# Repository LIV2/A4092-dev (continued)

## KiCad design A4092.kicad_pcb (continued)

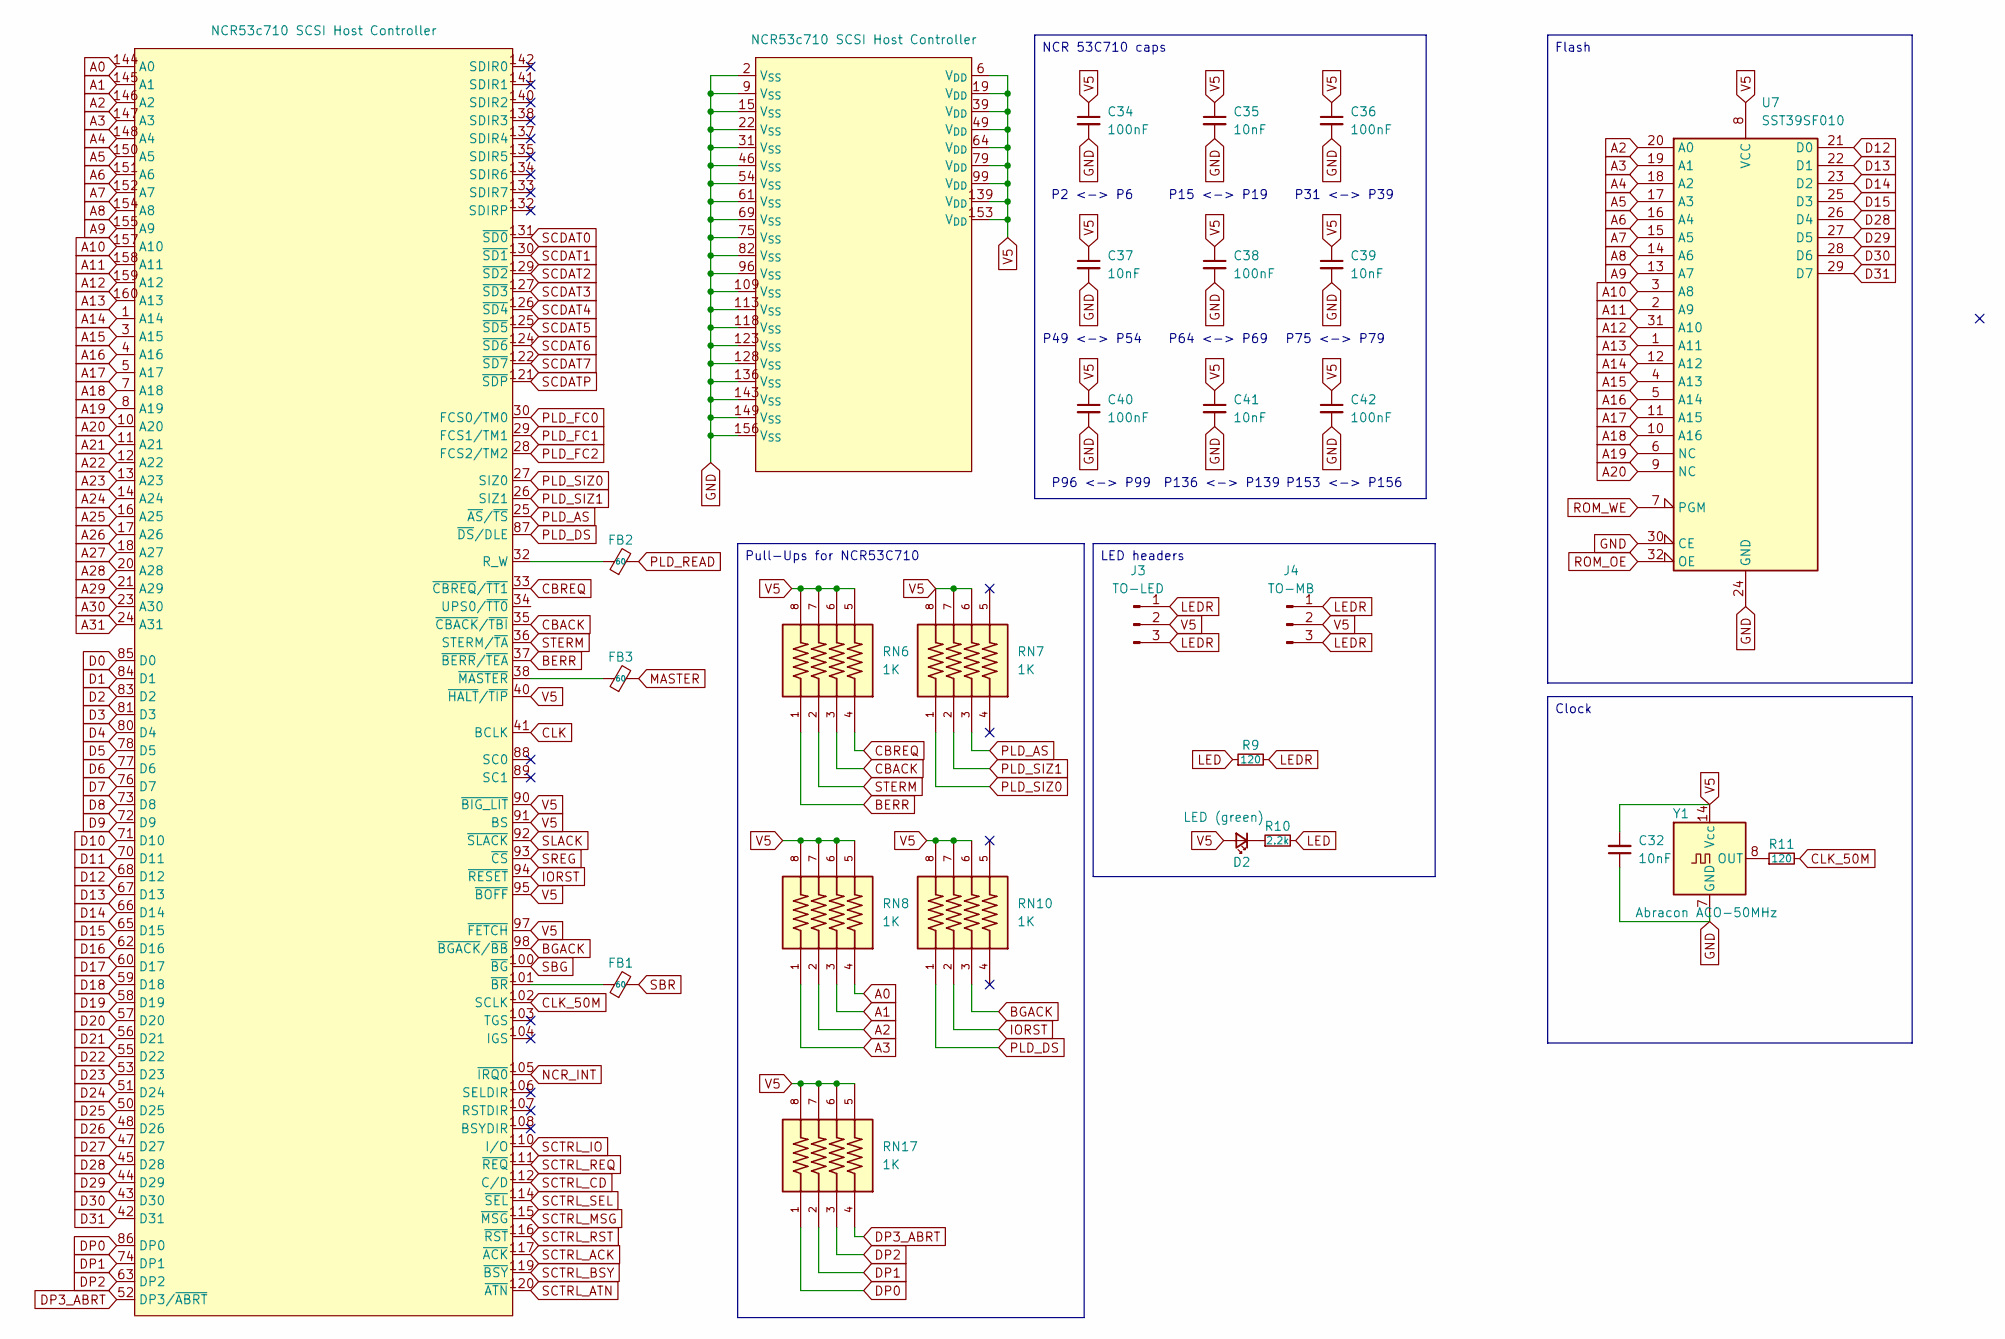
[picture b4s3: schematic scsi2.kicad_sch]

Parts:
C32, C35, C37, C39, C41: 10nF; C_0603_1608Metric_Pad1.08x0.95mm_HandSolder
C34, C36, C38, C40, C42: 100nF; C_0603_1608Metric_Pad1.08x0.95mm_HandSolder
D2: LED (green); LED_0805_2012Metric
FB1, FB2, FB3: 60; C_0603_1608Metric_Pad1.08x0.95mm_HandSolder
J3: TO-LED; PinHeader_1x03_P2.54mm_Vertical
J4: TO-MB; PinHeader_1x03_P2.54mm_Vertical
R9, R11: 120; R_0603_1608Metric
R10: 2.2k; R_0603_1608Metric
RN6, RN7, RN8, RN10, RN17: 1K; BO_CAY16; PARTREV V.9
U4: NCR53c710 SCSI Host Controller; PQFP-160_28x28mm_P0.65mm
U7: SST39SF010; TSSOP-32_8x11mm_P0.65mm
Y1: Abracon ACO-50MHz; Oscillator_DIP-14

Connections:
A0: RN8.4, U4.144 (A0); also elsewhere on the board
A1: RN8.3, U4.145 (A1); also elsewhere on the board
A2: RN8.2, U4.146 (A2), U7.20 (A0); also elsewhere on the board
A3: RN8.1, U4.147 (A3), U7.19 (A1); also elsewhere on the board
A4: U4.148 (A4), U7.18 (A2); also elsewhere on the board
A5: U4.150 (A5), U7.17 (A3); also elsewhere on the board
A6: U4.151 (A6), U7.16 (A4); also elsewhere on the board
A7: U4.152 (A7), U7.15 (A5); also elsewhere on the board
A8: U4.154 (A8), U7.14 (A6); also elsewhere on the board
A9: U4.155 (A9), U7.13 (A7); also elsewhere on the board
A10: U4.157 (A10), U7.3 (A8); also elsewhere on the board
A11: U4.158 (A11), U7.2 (A9); also elsewhere on the board
A12: U4.159 (A12), U7.31 (A10); also elsewhere on the board
A13: U4.160 (A13), U7.1 (A11); also elsewhere on the board
A14: U4.1 (A14), U7.12 (A12); also elsewhere on the board
A15: U4.3 (A15), U7.4 (A13); also elsewhere on the board
A16: U4.4 (A16), U7.5 (A14); also elsewhere on the board
A17: U4.5 (A17), U7.11 (A15); also elsewhere on the board
A18: U4.7 (A18), U7.10 (A16); also elsewhere on the board
A19: U4.8 (A19), U7.6 (NC); also elsewhere on the board
A20: U4.10 (A20), U7.9 (NC); also elsewhere on the board
A21: U4.11 (A21); also elsewhere on the board
A22: U4.12 (A22); also elsewhere on the board
A23: U4.13 (A23); also elsewhere on the board
A24: U4.14 (A24); also elsewhere on the board
A25: U4.16 (A25); also elsewhere on the board
A26: U4.17 (A26); also elsewhere on the board
A27: U4.18 (A27); also elsewhere on the board
A28: U4.20 (A28); also elsewhere on the board
A29: U4.21 (A29); also elsewhere on the board
A30: U4.23 (A30); also elsewhere on the board
A31: U4.24 (A31); also elsewhere on the board
BERR: RN6.1, U4.37 (~BERR/~TEA); also elsewhere on the board
BGACK: RN10.3, U4.98 (~BGACK/~BB)
CBACK: RN6.3, U4.35 (~CBACK/~TBI); also elsewhere on the board
CBREQ: RN6.4, U4.33 (~CBREQ/~TT1); also elsewhere on the board
CLK: U4.41 (BCLK); also elsewhere on the board
CLK_50M: R11.2, U4.102 (SCLK); also elsewhere on the board
D0: U4.85 (D0); also elsewhere on the board
D1: U4.84 (D1); also elsewhere on the board
D2: U4.83 (D2); also elsewhere on the board
D3: U4.81 (D3); also elsewhere on the board
D4: U4.80 (D4); also elsewhere on the board
D5: U4.78 (D5); also elsewhere on the board
D6: U4.77 (D6); also elsewhere on the board
D7: U4.76 (D7); also elsewhere on the board
D8: U4.73 (D8); also elsewhere on the board
D9: U4.72 (D9); also elsewhere on the board
D10: U4.71 (D10); also elsewhere on the board
D11: U4.70 (D11); also elsewhere on the board
D12: U4.68 (D12), U7.21 (D0); also elsewhere on the board
D13: U4.67 (D13), U7.22 (D1); also elsewhere on the board
D14: U4.66 (D14), U7.23 (D2); also elsewhere on the board
D15: U4.65 (D15), U7.25 (D3); also elsewhere on the board
D16: U4.62 (D16); also elsewhere on the board
D17: U4.60 (D17); also elsewhere on the board
D18: U4.59 (D18); also elsewhere on the board
D19: U4.58 (D19); also elsewhere on the board
D20: U4.57 (D20); also elsewhere on the board
D21: U4.56 (D21); also elsewhere on the board
D22: U4.55 (D22); also elsewhere on the board
D23: U4.53 (D23); also elsewhere on the board
D24: U4.51 (D24); also elsewhere on the board
D25: U4.50 (D25); also elsewhere on the board
D26: U4.48 (D26); also elsewhere on the board
D27: U4.47 (D27); also elsewhere on the board
D28: U4.45 (D28), U7.26 (D4); also elsewhere on the board
D29: U4.44 (D29), U7.27 (D5); also elsewhere on the board
D30: U4.43 (D30), U7.28 (D6); also elsewhere on the board
D31: U4.42 (D31), U7.29 (D7); also elsewhere on the board
DP0: RN17.1, U4.86 (DP0)
DP1: RN17.2, U4.74 (DP1)
DP2: RN17.3, U4.63 (DP2)
DP3_ABRT: RN17.4, U4.52 (DP3/~ABRT)
IORST: RN10.2, U4.94 (~RESET); also elsewhere on the board
LED: R9.1, R10.2; also elsewhere on the board
LEDR: J3.1, J3.3, J4.1, J4.3, R9.2; also elsewhere on the board
MASTER: FB3.2; also elsewhere on the board
NCR_INT: U4.105 (~IRQ0); also elsewhere on the board
unnamed: D2.1 (K), R10.1
unnamed: FB2.1, U4.32 (R_W)
unnamed: FB1.1, U4.101 (~BR)
unnamed: FB3.1, U4.38 (~MASTER)
unnamed: R11.1, Y1.3 (OUT), Y1.8 (OUT)
PLD_AS: RN7.3, U4.25 (~AS/~TS); also elsewhere on the board
PLD_DS: RN10.1, U4.87 (~DS/DLE); also elsewhere on the board
PLD_FC0: U4.30 (FCS0/TM0); also elsewhere on the board
PLD_FC1: U4.29 (FCS1/TM1); also elsewhere on the board
PLD_FC2: U4.28 (FCS2/TM2); also elsewhere on the board
PLD_READ: FB2.2; also elsewhere on the board
PLD_SIZ0: RN7.1, U4.27 (SIZ0); also elsewhere on the board
PLD_SIZ1: RN7.2, U4.26 (SIZ1); also elsewhere on the board
ROM_OE: U7.32 (OE); also elsewhere on the board
ROM_WE: U7.7 (PGM)
SBG: U4.100 (~BG); also elsewhere on the board
SBR: FB1.2; also elsewhere on the board
SCDAT0: U4.131 (~SD0); also elsewhere on the board
SCDAT1: U4.130 (~SD1); also elsewhere on the board
SCDAT2: U4.129 (~SD2); also elsewhere on the board
SCDAT3: U4.127 (~SD3); also elsewhere on the board
SCDAT4: U4.126 (~SD4); also elsewhere on the board
SCDAT5: U4.125 (~SD5); also elsewhere on the board
SCDAT6: U4.124 (~SD6); also elsewhere on the board
SCDAT7: U4.122 (~SD7); also elsewhere on the board
SCDATP: U4.121 (~SDP); also elsewhere on the board
SCTRL_ACK: U4.117 (~ACK); also elsewhere on the board
SCTRL_ATN: U4.120 (~ATN); also elsewhere on the board
SCTRL_BSY: U4.119 (~BSY); also elsewhere on the board
SCTRL_CD: U4.112 (C/D); also elsewhere on the board
SCTRL_IO: U4.110 (I/O); also elsewhere on the board
SCTRL_MSG: U4.115 (~MSG); also elsewhere on the board
SCTRL_REQ: U4.111 (~REQ); also elsewhere on the board
SCTRL_RST: U4.116 (~RST); also elsewhere on the board
SCTRL_SEL: U4.114 (~SEL); also elsewhere on the board
SLACK: U4.92 (~SLACK); also elsewhere on the board
SREG: U4.93 (~CS); also elsewhere on the board
STERM: RN6.2, U4.36 (STERM/~TA); also elsewhere on the board
V5: C32.2, C34.1, C35.1, C36.1, C37.1, C38.1, C39.1, C40.1, C41.1, C42.1, D2.2 (A), J3.2, J4.2, RN6.5, RN6.6, RN6.7, RN6.8, RN7.6, RN7.7, RN7.8, RN8.5, RN8.6, RN8.7, RN8.8, RN10.6, RN10.7, RN10.8, RN17.5, RN17.6, RN17.7, RN17.8, U4.6 (V_{DD}), U4.19 (V_{DD}), U4.39 (V_{DD}), U4.40 (~HALT/~TIP), U4.49 (V_{DD}), U4.64 (V_{DD}), U4.79 (V_{DD}), U4.90 (~BIG_LIT), U4.91 (BS), U4.95 (~BOFF), U4.97 (~FETCH), U4.99 (V_{DD}), U4.139 (V_{DD}), U4.153 (V_{DD}), U7.8 (VCC), Y1.4 (VDD), Y1.14 (Vcc); also elsewhere on the board

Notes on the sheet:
P2 <-> P6
P96 <-> P99
P49 <-> P54
P136 <-> P139
P153 <-> P156
P31 <-> P39
P64 <-> P69
P15 <-> P19
P75 <-> P79
LED headers
NCR 53C710 caps
Clock
Flash
Pull-Ups for NCR53C710

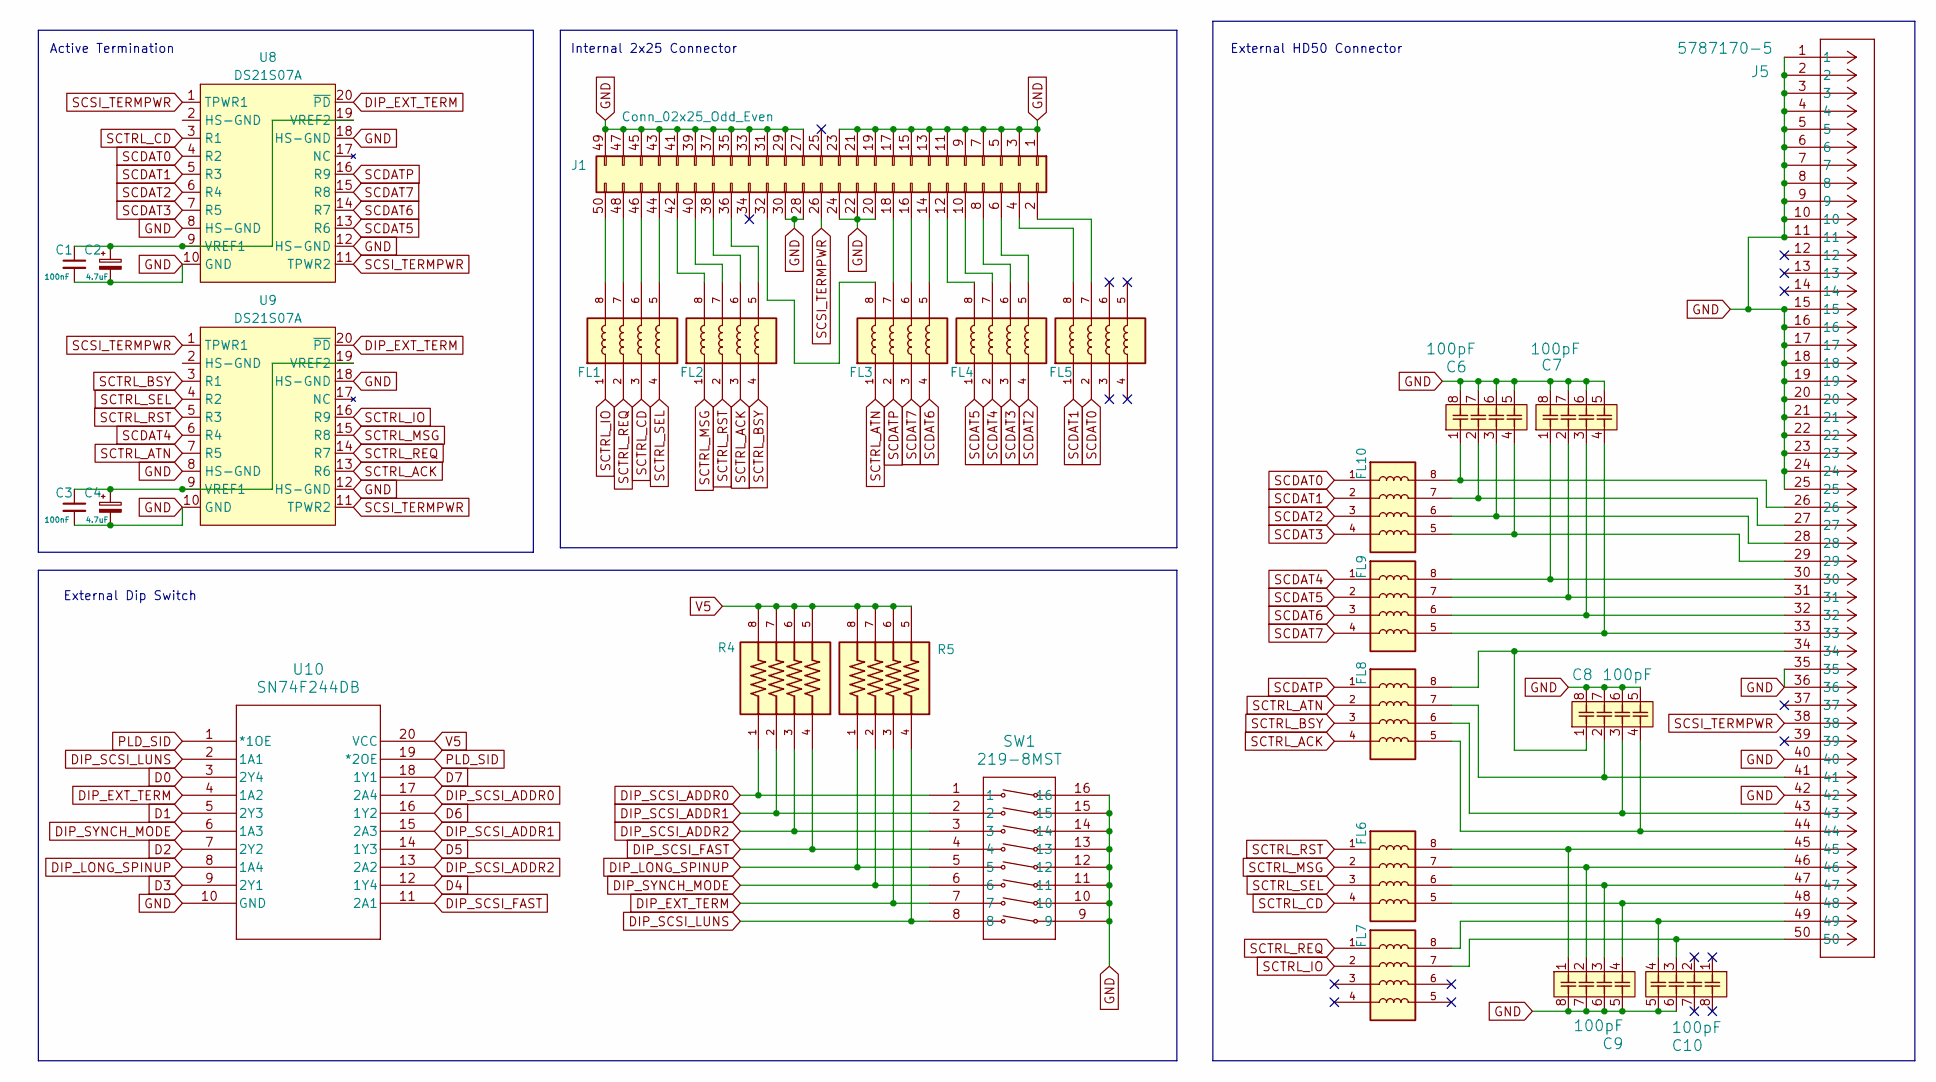
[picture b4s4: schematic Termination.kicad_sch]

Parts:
C1, C3: 100nF; C_0603_1608Metric_Pad1.08x0.95mm_HandSolder
C2, C4: 4.7uF; CP_Elec_4x5.7
C6, C7, C8, C9, C10: 100pF; CAP_CA0612_3P2X1P6_YAG
FL1, FL2, FL3, FL4, FL5, FL6, FL7, FL8, FL9, FL10: DA1206D600R-10; FB_DA1206D600R-10; PARTREV F; DigiKey_Part_Number 240-2539-2-ND
J1: Conn_02x25_Odd_Even; IDC-Header_2x25_P2.54mm_Vertical
J5: 5787170-5; CONN_5787170-5_TYC
R4, R5: YC324-FK-071KL; RESCAXS127P508X320X70-8N; PARTREV V.9
SW1: 219-8MST; SO16_219-8_CTS
U8, U9: DS21S07A; TSSOP-20_4.4x6.5mm_P0.65mm
U10: SN74F244DB; DB20

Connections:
D0: U10.3 (2Y4); also elsewhere on the board
D1: U10.5 (2Y3); also elsewhere on the board
D2: U10.7 (2Y2); also elsewhere on the board
D3: U10.9 (2Y1); also elsewhere on the board
D4: U10.12 (1Y4); also elsewhere on the board
D5: U10.14 (1Y3); also elsewhere on the board
D6: U10.16 (1Y2); also elsewhere on the board
D7: U10.18 (1Y1); also elsewhere on the board
DIP_EXT_TERM: R5.3, SW1.7, U8.20 (~PD), U9.20 (~PD), U10.4 (1A2); also elsewhere on the board
DIP_LONG_SPINUP: R5.1, SW1.5, U10.8 (1A4); also elsewhere on the board
DIP_SCSI_ADDR0: R4.1, SW1.1, U10.17 (2A4); also elsewhere on the board
DIP_SCSI_ADDR1: R4.2, SW1.2, U10.15 (2A3); also elsewhere on the board
DIP_SCSI_ADDR2: R4.3, SW1.3, U10.13 (2A2); also elsewhere on the board
DIP_SCSI_FAST: R4.4, SW1.4, U10.11 (2A1); also elsewhere on the board
DIP_SCSI_LUNS: R5.4, SW1.8, U10.2 (1A1); also elsewhere on the board
DIP_SYNCH_MODE: R5.2, SW1.6, U10.6 (1A3); also elsewhere on the board
unnamed: C6.1, FL10.8, J5.26
unnamed: C6.2, FL10.7, J5.27
unnamed: C6.3, FL10.6, J5.28
unnamed: C6.4, FL10.5, J5.29
unnamed: C7.1, FL9.8, J5.30
unnamed: C7.2, FL9.7, J5.31
unnamed: C7.3, FL9.6, J5.32
unnamed: C7.4, FL9.5, J5.33
unnamed: C8.1, FL8.8, J5.34
unnamed: C8.2, FL8.7, J5.41
unnamed: C8.3, FL8.6, J5.43
unnamed: C8.4, FL8.5, J5.44
unnamed: C9.1, FL6.8, J5.45
unnamed: C9.2, FL6.7, J5.46
unnamed: C9.3, FL6.6, J5.47
unnamed: C9.4, FL6.5, J5.48
unnamed: C10.3, FL7.7, J5.50
unnamed: C10.4, FL7.8, J5.49
unnamed: FL5.7, J1.2
unnamed: FL5.8, J1.4
unnamed: FL4.5, J1.6
unnamed: FL4.6, J1.8
unnamed: FL4.7, J1.10
unnamed: FL4.8, J1.12
unnamed: FL3.5, J1.14
unnamed: FL3.6, J1.16
unnamed: FL3.7, J1.18
unnamed: FL3.8, J1.32
unnamed: FL2.5, J1.36
unnamed: FL2.6, J1.38
unnamed: FL2.7, J1.40
unnamed: FL2.8, J1.42
unnamed: FL1.5, J1.44
unnamed: FL1.6, J1.46
unnamed: FL1.7, J1.48
unnamed: FL1.8, J1.50
unnamed: C1.1, C2.1, U8.9 (VREF1), U8.19 (VREF2)
unnamed: C3.1, C4.1, U9.9 (VREF1), U9.19 (VREF2)
PLD_SID: U10.1 (*1OE), U10.19 (*2OE); also elsewhere on the board
SCDAT0: FL5.2, FL10.1, U8.4 (R2); also elsewhere on the board
SCDAT1: FL5.1, FL10.2, U8.5 (R3); also elsewhere on the board
SCDAT2: FL4.4, FL10.3, U8.6 (R4); also elsewhere on the board
SCDAT3: FL4.3, FL10.4, U8.7 (R5); also elsewhere on the board
SCDAT4: FL4.2, FL9.1, U9.6 (R4); also elsewhere on the board
SCDAT5: FL4.1, FL9.2, U8.13 (R6); also elsewhere on the board
SCDAT6: FL3.4, FL9.3, U8.14 (R7); also elsewhere on the board
SCDAT7: FL3.3, FL9.4, U8.15 (R8); also elsewhere on the board
SCDATP: FL3.2, FL8.1, U8.16 (R9); also elsewhere on the board
SCSI_TERMPWR: J1.26, J5.38, U8.1 (TPWR1), U8.11 (TPWR2), U9.1 (TPWR1), U9.11 (TPWR2); also elsewhere on the board
SCTRL_ACK: FL2.3, FL8.4, U9.13 (R6); also elsewhere on the board
SCTRL_ATN: FL3.1, FL8.2, U9.7 (R5); also elsewhere on the board
SCTRL_BSY: FL2.4, FL8.3, U9.3 (R1); also elsewhere on the board
SCTRL_CD: FL1.3, FL6.4, U8.3 (R1); also elsewhere on the board
SCTRL_IO: FL1.1, FL7.2, U9.16 (R9); also elsewhere on the board
SCTRL_MSG: FL2.1, FL6.2, U9.15 (R8); also elsewhere on the board
SCTRL_REQ: FL1.2, FL7.1, U9.14 (R7); also elsewhere on the board
SCTRL_RST: FL2.2, FL6.1, U9.5 (R3); also elsewhere on the board
SCTRL_SEL: FL1.4, FL6.3, U9.4 (R2); also elsewhere on the board
V5: R4.5, R4.6, R4.7, R4.8, R5.5, R5.6, R5.7, R5.8, U10.20 (VCC); also elsewhere on the board

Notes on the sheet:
Active Termination
Internal 2x25 Connector
External HD50 Connector
External Dip Switch

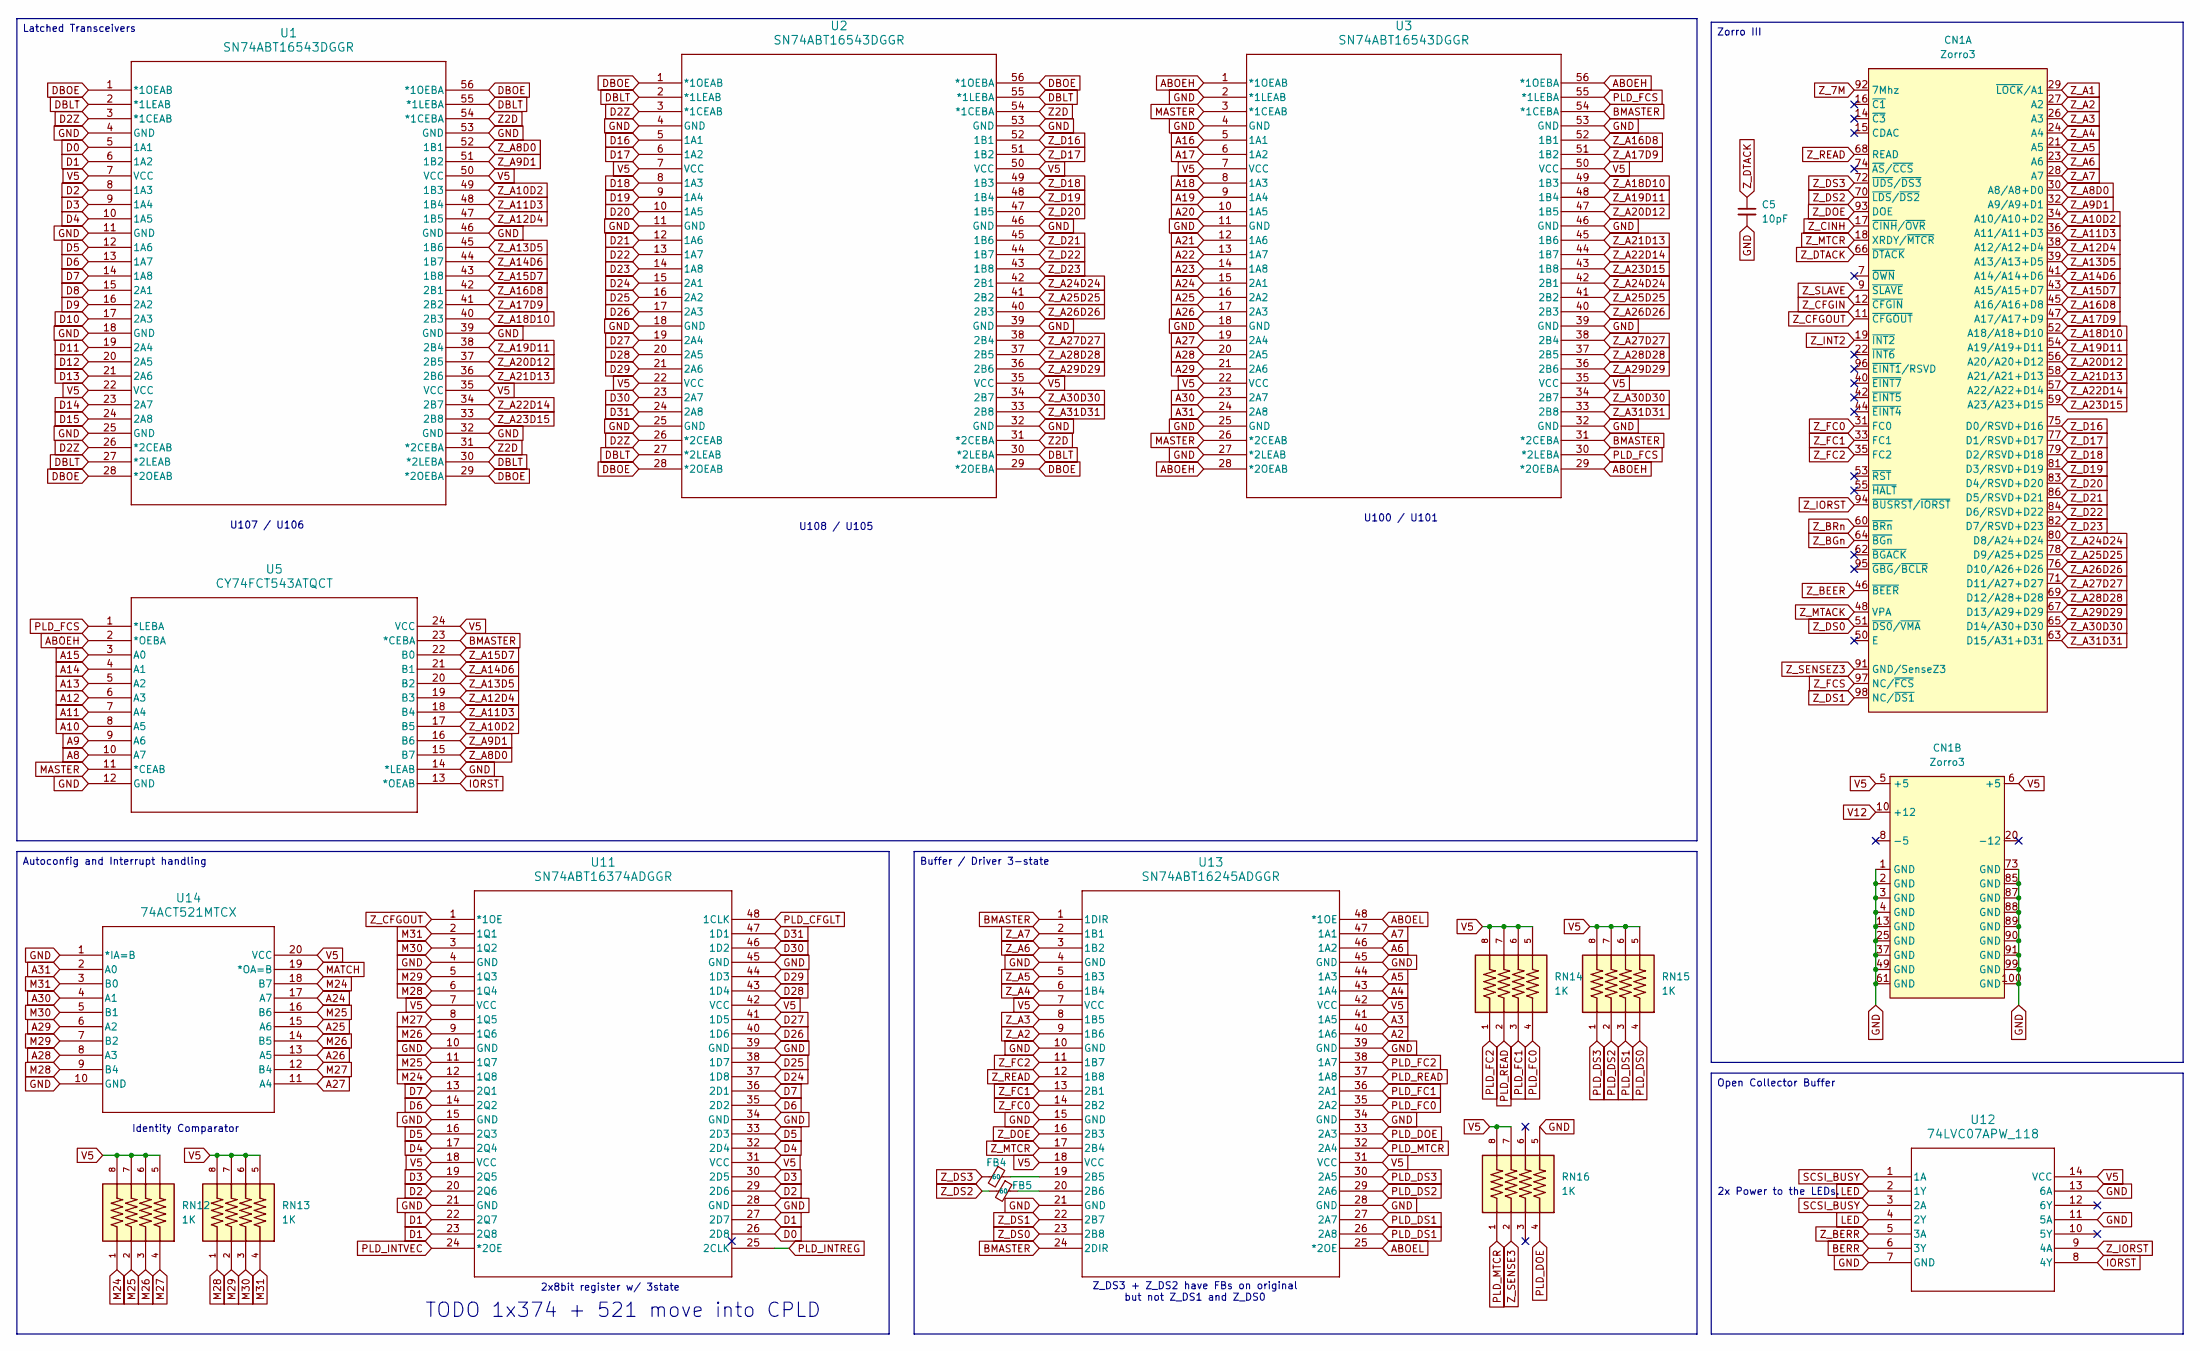
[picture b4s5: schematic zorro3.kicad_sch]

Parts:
C5: 10pF; C_0603_1608Metric_Pad1.08x0.95mm_HandSolder
CN1: Zorro3; Zorro3-CardEdge
FB4, FB5: 60; C_0603_1608Metric_Pad1.08x0.95mm_HandSolder
RN12, RN13, RN14, RN15, RN16: 1K; BO_CAY16; PARTREV V.9
U1, U2, U3: SN74ABT16543DGGR; DL56
U5: CY74FCT543ATQCT; DBQ24
U11: SN74ABT16374ADGGR; DGG48
U12: 74LVC07APW_118; TSSOP14_5P1X4P5_NEX
U13: SN74ABT16245ADGGR; DGG48
U14: 74ACT521MTCX; TSSOP20_4P4X6P5_ONS

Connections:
A2: U13.40 (1A6); also elsewhere on the board
A3: U13.41 (1A5); also elsewhere on the board
A4: U13.43 (1A4); also elsewhere on the board
A5: U13.44 (1A3); also elsewhere on the board
A6: U13.46 (1A2); also elsewhere on the board
A7: U13.47 (1A1); also elsewhere on the board
A16: U3.5 (1A1); also elsewhere on the board
A17: U3.6 (1A2); also elsewhere on the board
A18: U3.8 (1A3); also elsewhere on the board
A19: U3.9 (1A4); also elsewhere on the board
A20: U3.10 (1A5); also elsewhere on the board
A21: U3.12 (1A6); also elsewhere on the board
A22: U3.13 (1A7); also elsewhere on the board
A23: U3.14 (1A8); also elsewhere on the board
A24: U3.15 (2A1), U14.17 (A7); also elsewhere on the board
A25: U3.16 (2A2), U14.15 (A6); also elsewhere on the board
A26: U3.17 (2A3), U14.13 (A5); also elsewhere on the board
A27: U3.19 (2A4), U14.11 (A4); also elsewhere on the board
A28: U3.20 (2A5), U14.8 (A3); also elsewhere on the board
A29: U3.21 (2A6), U14.6 (A2); also elsewhere on the board
A30: U3.23 (2A7), U14.4 (A1); also elsewhere on the board
A31: U3.24 (2A8), U14.2 (A0); also elsewhere on the board
ABOEH: U3.1 (*1OEAB), U3.28 (*2OEAB), U3.29 (*2OEBA), U3.56 (*1OEBA), U5.2 (*OEBA); also elsewhere on the board
ABOEL: U13.25 (*2OE), U13.48 (*1OE); also elsewhere on the board
BERR: U12.6 (3Y); also elsewhere on the board
BMASTER: U3.31 (*2CEBA), U3.54 (*1CEBA), U5.23 (*CEBA), U13.1 (1DIR), U13.24 (2DIR); also elsewhere on the board
D0: U1.5 (1A1), U11.26 (2D8); also elsewhere on the board
D1: U1.6 (1A2), U11.22 (2Q7), U11.23 (2Q8), U11.27 (2D7); also elsewhere on the board
D2: U1.8 (1A3), U11.20 (2Q6), U11.29 (2D6); also elsewhere on the board
D2Z: U1.3 (*1CEAB), U1.26 (*2CEAB), U2.3 (*1CEAB), U2.26 (*2CEAB); also elsewhere on the board
D3: U1.9 (1A4), U11.19 (2Q5), U11.30 (2D5); also elsewhere on the board
D4: U1.10 (1A5), U11.17 (2Q4), U11.32 (2D4); also elsewhere on the board
D5: U1.12 (1A6), U11.16 (2Q3), U11.33 (2D3); also elsewhere on the board
D6: U1.13 (1A7), U11.14 (2Q2), U11.35 (2D2); also elsewhere on the board
D7: U1.14 (1A8), U11.13 (2Q1), U11.36 (2D1); also elsewhere on the board
D8: U1.15 (2A1); also elsewhere on the board
D9: U1.16 (2A2); also elsewhere on the board
D10: U1.17 (2A3); also elsewhere on the board
D11: U1.19 (2A4); also elsewhere on the board
D12: U1.20 (2A5); also elsewhere on the board
D13: U1.21 (2A6); also elsewhere on the board
D14: U1.23 (2A7); also elsewhere on the board
D15: U1.24 (2A8); also elsewhere on the board
D16: U2.5 (1A1); also elsewhere on the board
D17: U2.6 (1A2); also elsewhere on the board
D18: U2.8 (1A3); also elsewhere on the board
D19: U2.9 (1A4); also elsewhere on the board
D20: U2.10 (1A5); also elsewhere on the board
D21: U2.12 (1A6); also elsewhere on the board
D22: U2.13 (1A7); also elsewhere on the board
D23: U2.14 (1A8); also elsewhere on the board
D24: U2.15 (2A1), U11.37 (1D8); also elsewhere on the board
D25: U2.16 (2A2), U11.38 (1D7); also elsewhere on the board
D26: U2.17 (2A3), U11.40 (1D6); also elsewhere on the board
D27: U2.19 (2A4), U11.41 (1D5); also elsewhere on the board
D28: U2.20 (2A5), U11.43 (1D4); also elsewhere on the board
D29: U2.21 (2A6), U11.44 (1D3); also elsewhere on the board
D30: U2.23 (2A7), U11.46 (1D2); also elsewhere on the board
D31: U2.24 (2A8), U11.47 (1D1); also elsewhere on the board
DBLT: U1.2 (*1LEAB), U1.27 (*2LEAB), U1.30 (*2LEBA), U1.55 (*1LEBA), U2.2 (*1LEAB), U2.27 (*2LEAB), U2.30 (*2LEBA), U2.55 (*1LEBA); also elsewhere on the board
DBOE: U1.1 (*1OEAB), U1.28 (*2OEAB), U1.29 (*2OEBA), U1.56 (*1OEBA), U2.1 (*1OEAB), U2.28 (*2OEAB), U2.29 (*2OEBA), U2.56 (*1OEBA); also elsewhere on the board
IORST: U5.13 (*OEAB), U12.8 (4Y); also elsewhere on the board
LED: U12.2 (1Y), U12.4 (2Y); also elsewhere on the board
MASTER: U3.3 (*1CEAB), U3.26 (*2CEAB), U5.11 (*CEAB); also elsewhere on the board
unnamed: RN12.1, U11.12 (1Q8), U14.18 (B7)
unnamed: RN12.2, U11.11 (1Q7), U14.16 (B6)
unnamed: RN12.3, U11.9 (1Q6), U14.14 (B5)
unnamed: RN12.4, U11.8 (1Q5), U14.12 (B4)
unnamed: RN13.1, U11.6 (1Q4), U14.9 (B4)
unnamed: RN13.2, U11.5 (1Q3), U14.7 (B2)
unnamed: RN13.3, U11.3 (1Q2), U14.5 (B1)
unnamed: RN13.4, U11.2 (1Q1), U14.3 (B0)
unnamed: FB4.1, U13.19 (2B5)
unnamed: FB5.1, U13.20 (2B6)
PLD_DOE: RN16.4, U13.33 (2A3); also elsewhere on the board
PLD_DS0: RN15.4; also elsewhere on the board
PLD_DS1: RN15.3, U13.26 (2A8), U13.27 (2A7); also elsewhere on the board
PLD_DS2: RN15.2, U13.29 (2A6); also elsewhere on the board
PLD_DS3: RN15.1, U13.30 (2A5); also elsewhere on the board
PLD_FC0: RN14.4, U13.35 (2A2); also elsewhere on the board
PLD_FC1: RN14.3, U13.36 (2A1); also elsewhere on the board
PLD_FC2: RN14.1, U13.38 (1A7); also elsewhere on the board
PLD_FCS: U3.30 (*2LEBA), U3.55 (*1LEBA), U5.1 (*LEBA); also elsewhere on the board
PLD_MTCR: RN16.1, U13.32 (2A4); also elsewhere on the board
PLD_READ: RN14.2, U13.37 (1A8); also elsewhere on the board
SCSI_BUSY: U12.1 (1A), U12.3 (2A)
V5: CN1.5 (+5), CN1.6 (+5), RN12.5, RN12.6, RN12.7, RN12.8, RN13.5, RN13.6, RN13.7, RN13.8, RN14.5, RN14.6, RN14.7, RN14.8, RN15.5, RN15.6, RN15.7, RN15.8, RN16.7, RN16.8, U1.7 (VCC), U1.22 (VCC), U1.35 (VCC), U1.50 (VCC), U2.7 (VCC), U2.22 (VCC), U2.35 (VCC), U2.50 (VCC), U3.7 (VCC), U3.22 (VCC), U3.35 (VCC), U3.50 (VCC), U5.24 (VCC), U11.7 (VCC), U11.18 (VCC), U11.31 (VCC), U11.42 (VCC), U12.14 (VCC), U13.7 (VCC), U13.18 (VCC), U13.31 (VCC), U13.42 (VCC), U14.20 (VCC); also elsewhere on the board
V12: CN1.10 (+12); also elsewhere on the board
Z2D: U1.31 (*2CEBA), U1.54 (*1CEBA), U2.31 (*2CEBA), U2.54 (*1CEBA); also elsewhere on the board
Z_7M: CN1.92 (7Mhz); also elsewhere on the board
Z_A1: CN1.29 (~LOCK/A1)
Z_A2: CN1.27 (A2), U13.9 (1B6)
Z_A3: CN1.26 (A3), U13.8 (1B5)
Z_A4: CN1.24 (A4), U13.6 (1B4)
Z_A5: CN1.21 (A5), U13.5 (1B3)
Z_A6: CN1.23 (A6), U13.3 (1B2)
Z_A7: CN1.28 (A7), U13.2 (1B1)
Z_A8D0: CN1.30 (A8/A8+D0), U1.52 (1B1), U5.15 (B7); also elsewhere on the board
Z_A9D1: CN1.32 (A9/A9+D1), U1.51 (1B2), U5.16 (B6); also elsewhere on the board
Z_A10D2: CN1.34 (A10/A10+D2), U1.49 (1B3), U5.17 (B5); also elsewhere on the board
Z_A11D3: CN1.36 (A11/A11+D3), U1.48 (1B4), U5.18 (B4); also elsewhere on the board
Z_A12D4: CN1.38 (A12/A12+D4), U1.47 (1B5), U5.19 (B3); also elsewhere on the board
Z_A13D5: CN1.39 (A13/A13+D5), U1.45 (1B6), U5.20 (B2); also elsewhere on the board
Z_A14D6: CN1.41 (A14/A14+D6), U1.44 (1B7), U5.21 (B1); also elsewhere on the board
Z_A15D7: CN1.43 (A15/A15+D7), U1.43 (1B8), U5.22 (B0); also elsewhere on the board
Z_A16D8: CN1.45 (A16/A16+D8), U1.42 (2B1), U3.52 (1B1)
Z_A17D9: CN1.47 (A17/A17+D9), U1.41 (2B2), U3.51 (1B2)
Z_A18D10: CN1.52 (A18/A18+D10), U1.40 (2B3), U3.49 (1B3)
Z_A19D11: CN1.54 (A19/A19+D11), U1.38 (2B4), U3.48 (1B4)
Z_A20D12: CN1.56 (A20/A20+D12), U1.37 (2B5), U3.47 (1B5)
Z_A21D13: CN1.58 (A21/A21+D13), U1.36 (2B6), U3.45 (1B6)
Z_A22D14: CN1.57 (A22/A22+D14), U1.34 (2B7), U3.44 (1B7)
Z_A23D15: CN1.59 (A23/A23+D15), U1.33 (2B8), U3.43 (1B8)
Z_A24D24: CN1.80 (D8/A24+D24), U2.42 (2B1), U3.42 (2B1)
Z_A25D25: CN1.78 (D9/A25+D25), U2.41 (2B2), U3.41 (2B2)
Z_A26D26: CN1.76 (D10/A26+D26), U2.40 (2B3), U3.40 (2B3)
Z_A27D27: CN1.71 (D11/A27+D27), U2.38 (2B4), U3.38 (2B4)
Z_A28D28: CN1.69 (D12/A28+D28), U2.37 (2B5), U3.37 (2B5)
Z_A29D29: CN1.67 (D13/A29+D29), U2.36 (2B6), U3.36 (2B6)
Z_A30D30: CN1.65 (D14/A30+D30), U2.34 (2B7), U3.34 (2B7)
Z_A31D31: CN1.63 (D15/A31+D31), U2.33 (2B8), U3.33 (2B8)
Z_BEER: CN1.46 (~BEER)
Z_BERR: U12.5 (3A)
Z_BGn: CN1.64 (~BGn); also elsewhere on the board
Z_BRn: CN1.60 (~BRn); also elsewhere on the board
Z_CFGIN: CN1.12 (~CFGIN); also elsewhere on the board
Z_CFGOUT: CN1.11 (~CFGOUT), U11.1 (*1OE); also elsewhere on the board
Z_CINH: CN1.17 (~CINH/~OVR); also elsewhere on the board
Z_D16: CN1.75 (D0/RSVD+D16), U2.52 (1B1)
Z_D17: CN1.77 (D1/RSVD+D17), U2.51 (1B2)
Z_D18: CN1.79 (D2/RSVD+D18), U2.49 (1B3)
Z_D19: CN1.81 (D3/RSVD+D19), U2.48 (1B4)
Z_D20: CN1.83 (D4/RSVD+D20), U2.47 (1B5)
Z_D21: CN1.86 (D5/RSVD+D21), U2.45 (1B6)
Z_D22: CN1.84 (D6/RSVD+D22), U2.44 (1B7)
Z_D23: CN1.82 (D7/RSVD+D23), U2.43 (1B8)
Z_DOE: CN1.93 (DOE), U13.16 (2B3)
Z_DS0: CN1.51 (~DS0/~VMA), U13.23 (2B8)
Z_DS1: CN1.98 (NC/~DS1), U13.22 (2B7)
Z_DS2: CN1.70 (~LDS/~DS2), FB5.2
Z_DS3: CN1.72 (~UDS/~DS3), FB4.2
Z_DTACK: C5.1, CN1.66 (~DTACK); also elsewhere on the board
Z_FC0: CN1.31 (FC0), U13.14 (2B2)
Z_FC1: CN1.33 (FC1), U13.13 (2B1)
Z_FC2: CN1.35 (FC2), U13.11 (1B7)
Z_FCS: CN1.97 (NC/~FCS); also elsewhere on the board
Z_INT2: CN1.19 (~INT2); also elsewhere on the board
Z_IORST: CN1.94 (~BUSRST/~IORST), U12.9 (4A)
Z_MTACK: CN1.48 (VPA); also elsewhere on the board
Z_MTCR: CN1.18 (XRDY/~MTCR), U13.17 (2B4)
Z_READ: CN1.68 (READ), U13.12 (1B8)
Z_SENSE3: RN16.2
Z_SLAVE: CN1.9 (~SLAVE); also elsewhere on the board

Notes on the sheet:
Z_DS3 + Z_DS2 have FBs on original but not Z_DS1 and Z_DS0
TODO 1x374 + 521 move into CPLD
U100 / U101
Identity Comparator
U107 / U106
2x Power to the LEDs.
U108 / U105
2x8bit register w/ 3state
Buffer / Driver 3-state
Latched Transceivers
Open Collector Buffer
Autoconfig and Interrupt handling
Zorro III
